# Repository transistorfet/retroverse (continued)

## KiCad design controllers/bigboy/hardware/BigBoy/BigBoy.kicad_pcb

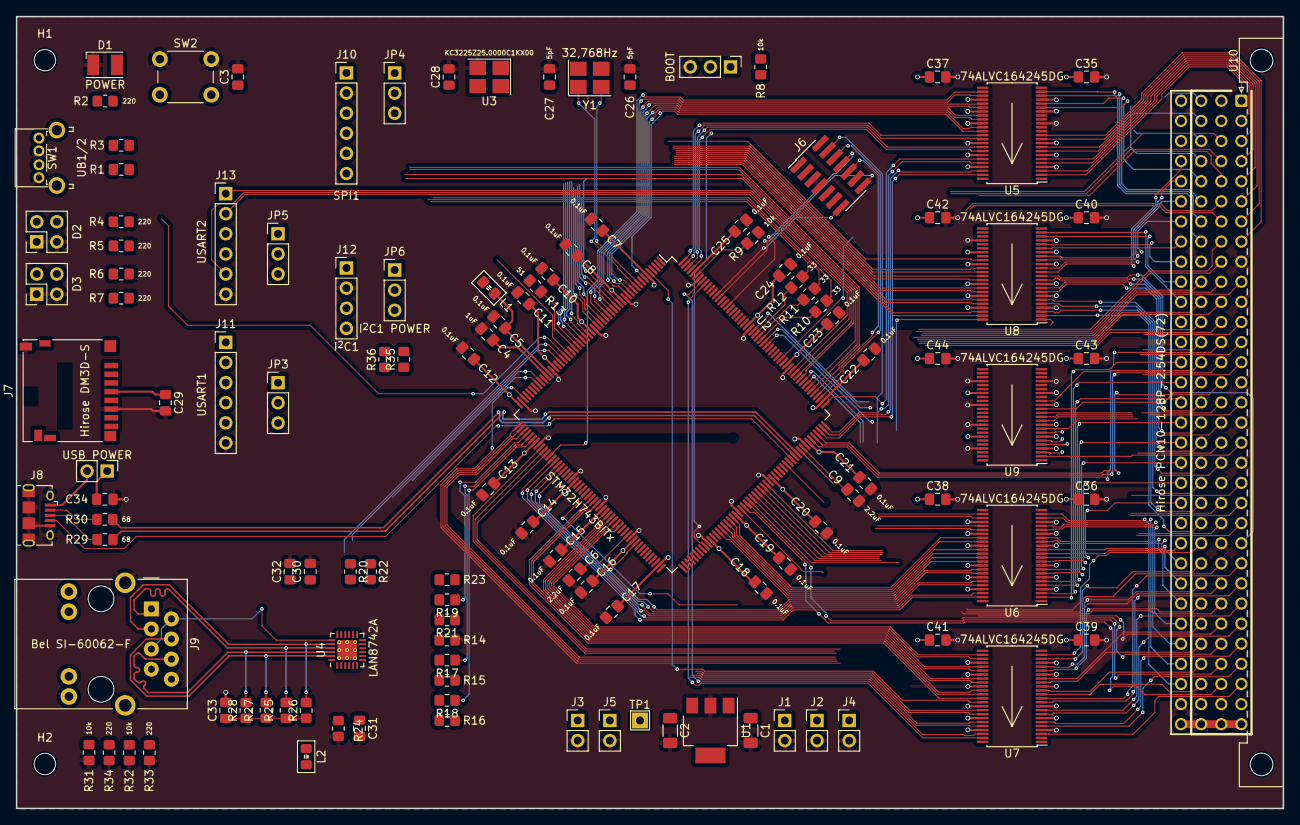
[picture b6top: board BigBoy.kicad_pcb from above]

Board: 4 copper layers, 160.0 x 100.0 mm, 120 parts (0 on the bottom side), 282 nets.

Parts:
C1, C2: 4.7uF; C_1206_3216Metric_Pad1.33x1.80mm_HandSolder
C3, C5, C7, C8, C10, C11, C12, C13, C14, C15, C16, C17, C18, C19, C20, C21, C22, C23, C24, C25, C28, C29, C30, C31, C32, C34, C35, C36, C37, C38, C39, C40, C41, C42, C43, C44: 0.1uF; C_0805_2012Metric_Pad1.18x1.45mm_HandSolder
C4: 1uF; C_0805_2012Metric_Pad1.18x1.45mm_HandSolder
C6, C9: 2.2uF; C_0805_2012Metric_Pad1.18x1.45mm_HandSolder
C26, C27: 5pF; C_0805_2012Metric_Pad1.18x1.45mm_HandSolder
C33: 10uF; C_0805_2012Metric_Pad1.18x1.45mm_HandSolder
D1: POWER; LED_PLCC-2_3.4x3.0mm_KA
D2: Dialight 5530188F; Dialight 553-0xxxF
D3: Dialight 5530177F; Dialight 553-0xxxF
H1, H2: MountingHole; MountingHole_2.7mm_M2.5_DIN965
J1, J2, J4: 5V; PinHeader_1x02_P2.54mm_Vertical
J3, J5: 3.3V; PinHeader_1x02_P2.54mm_Vertical
J6: Conn_ST_STDC14; PinHeader_2x07_P1.27mm_Vertical_SMD
J7: Hirose DM3D-S; microSD_HC_Hirose_DM3D-SF
J8: Amphenol 10118194-0001LF; USB_Micro-B_Amphenol_10118194_Horizontal
J9: Bel SI-60062-F; RJ45_Bel_SI-60062-F
J10: SPI1; PinHeader_1x06_P2.54mm_Vertical
J11: USART1; PinHeader_1x06_P2.54mm_Vertical
J12: I^{2}C1; PinHeader_1x04_P2.54mm_Vertical
J13: USART2; PinHeader_1x06_P2.54mm_Vertical
JP1: BOOT; PinHeader_1x03_P2.54mm_Vertical
JP2: USB POWER; PinHeader_1x02_P2.54mm_Vertical
JP3: USART1 POWER; PinHeader_1x03_P2.54mm_Vertical
JP4: SPI1 POWER; PinHeader_1x03_P2.54mm_Vertical
JP5: USART2 POWER; PinHeader_1x03_P2.54mm_Vertical
JP6: I^{2}C1 POWER; PinHeader_1x03_P2.54mm_Vertical
L1, L2: 600Ω @ 100MHz (MI0805K601R-10); Ferrite_0805_2012Metric_Pad1.15x1.40mm_BigPads
R1, R3, R8, R9, R14, R15, R16, R21, R22, R31, R32: 10k; R_0805_2012Metric_Pad1.20x1.40mm_HandSolder
R2, R4, R5, R6, R7, R33, R34: 220; R_0805_2012Metric_Pad1.20x1.40mm_HandSolder
R10, R11, R12, R17, R18, R19, R20: 33; R_0805_2012Metric_Pad1.20x1.40mm_HandSolder
R13: 51; R_0805_2012Metric_Pad1.20x1.40mm_HandSolder
R23: 1.5k; R_0805_2012Metric_Pad1.20x1.40mm_HandSolder
R24: 12.1k; R_0805_2012Metric_Pad1.20x1.40mm_HandSolder
R25, R26, R27, R28: 50; R_0805_2012Metric_Pad1.20x1.40mm_HandSolder
R29, R30: 68; R_0805_2012Metric_Pad1.20x1.40mm_HandSolder
R35, R36: 4.7k; R_0805_2012Metric_Pad1.20x1.40mm_HandSolder
SW1: UB1/2; E-Switch TL2243
SW2: ~{RESET}; SW_PUSH_6mm
TP1: 3.3V; TestPoint_THTPad_2.0x2.0mm_Drill1.0mm
U1: AP7361EA-33E-13; SOT-223
U2: STM32H743BITx; LQFP-208_28x28mm_P0.5mm
U3: KC3225Z25.0000C1KX00; Crystal_SMD_3225-4Pin_3.2x2.5mm_HandSoldering
U4: LAN8742A; VQFN-24-1EP_4x4mm_P0.5mm_EP2.5x2.5mm_ThermalVias
U5, U6, U7, U8, U9: 74ALVC164245DG; TSSOP-48_6.1x12.5mm_P0.5mm
U10: Hirose PCN10-128P-2.54DS(72); DIN41612_C_4x32_Male_Horizontal_THT
Y1: 32,768Hz; Crystal_SMD_3225-4Pin_3.2x2.5mm_HandSoldering

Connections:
+3.3V: C2.1, C7.1, C8.1, C10.1, C11.1, C12.1, C13.1, C14.1, C15.1, C16.1, C17.1, C18.1, C19.1, C20.1, C21.1, C22.1, C23.1, C24.1, C25.1, C28.1, C29.1, C30.1, C37.1, C38.1, C41.1, C42.1, C44.1, J3.1, J5.1, J6.3 (VCC), J7.4 (VDD), JP3.3 (B), JP4.3 (B), JP5.3 (B), JP6.3 (B), L1.2, L2.2, R1.1, R2.1, R3.1, R8.1, R9.1, R15.1, R16.1, R21.1, R22.1, R23.1, TP1.1, U1.3 (VO), U2.6 (VBAT), U2.15 (VDD), U2.26 (VDD), U2.39 (VDD), U2.52 (VDD), U2.59 (VDD), U2.73 (VDD), U2.83 (VDD), U2.94 (VDD), U2.103 (VDD), U2.115 (VDD), U2.124 (VDD), U2.137 (VDD33_USB), U2.150 (VDD), U2.158 (VDD), U2.171 (VDD), U2.185 (VDD), U2.204 (VDD), U3.1 (INH), U3.4 (VCC), U4.9 (VDDIO), U5.31 (VCCa), U5.42 (VCCa), U6.31 (VCCa), U6.42 (VCCa), U7.31 (VCCa), U7.42 (VCCa), U8.31 (VCCa), U8.42 (VCCa), U9.31 (VCCa), U9.42 (VCCa)
+5V: C1.1, C34.1, C35.2, C36.2, C39.2, C40.2, C43.2, J1.1, J2.1, J4.1, JP2.1 (A), JP3.1 (A), JP4.1 (A), JP5.1 (A), JP6.1 (A), U1.1 (VI), U5.7 (VCCb), U5.18 (VCCb), U6.7 (VCCb), U6.18 (VCCb), U7.7 (VCCb), U7.18 (VCCb), U8.7 (VCCb), U8.18 (VCCb), U9.7 (VCCb), U9.18 (VCCb), U10.a32 (+5V), U10.b32 (+5V), U10.c32 (+5V), U10.d1 (+5V), U10.d13 (+5V), U10.d32 (+5V)
/IO/RD+: J9.4 (RD+), R27.2, U4.23 (RXP)
/IO/RD-: J9.6 (RD-), R28.2, U4.22 (RXN)
/IO/TD+: J9.1 (TD+), R25.2, U4.21 (TXP)
/IO/TD-: J9.3 (TD-), R26.2, U4.20 (TXN)
AH_DIR: U2.54 (PA5), U6.24 (DIR2)
AL_DIR: U2.55 (PA6), U5.1 (DIR1), U5.24 (DIR2), U6.1 (DIR1)
CLK_25M: R13.2, U3.3 (CLK), U4.5 (XTAL1/CLKIN)
DH_DIR: U2.62 (PB1), U8.1 (DIR1), U8.24 (DIR2)
DL_DIR: U2.63 (PB2), U7.1 (DIR1), U7.24 (DIR2)
GND: C1.2, C2.2, C3.2, C4.1, C5.1, C6.2, C7.2, C8.2, C9.2, C10.2, C11.2, C12.2, C13.2, C14.2, C15.2, C16.2, C17.2, C18.2, C19.2, C20.2, C21.2, C22.2, C23.2, C24.2, C25.2, C26.2, C27.2, C28.2, C29.2, C30.2, C31.2, C32.2, C33.2, C34.2, C35.1, C36.1, C37.2, C38.2, C39.1, C40.1, C41.2, C42.2, C43.1, C44.2, D1.1 (K), D2.1 (A1), D2.3 (A2), D3.1 (A1), D3.3 (A2), J1.2, J2.2, J3.2, J4.2, J5.2, J6.5 (GND), J6.7 (GND), J6.11 (GNDDetect), J7.6 (VSS), J7.10 (SHIELD), J8.5 (GND), J8.6 (Shield), J9.8, J9.SH, J10.2, J11.6, J12.2, J13.6, JP1.3 (B), R14.2, R24.2, R31.2, R32.2, R33.2, R34.2, SW1.1 (C), SW1.3 (C), SW2.1, U1.2 (GND), U2.14 (VSS), U2.25 (VSS), U2.40 (VSSA), U2.51 (VSS), U2.60 (VSS), U2.72 (VSS), U2.82 (VSS), U2.93 (VSS), U2.114 (VSS), U2.125 (VSS), U2.136 (VSS), U2.149 (VSS), U2.170 (VSS), U2.184 (VSS), U2.202 (VSS), U3.2 (GND), U4.25 (VSS), U5.4 (GND), U5.10 (GND), U5.15 (GND), U5.21 (GND), U5.28 (GND), U5.34 (GND), U5.39 (GND), U5.45 (GND), U6.4 (GND), U6.10 (GND), U6.15 (GND), U6.21 (GND), U6.28 (GND), U6.34 (GND), U6.39 (GND), U6.45 (GND), U7.4 (GND), U7.10 (GND), U7.15 (GND), U7.21 (GND), U7.28 (GND), U7.34 (GND), U7.39 (GND), U7.45 (GND), U8.4 (GND), U8.10 (GND), U8.15 (GND), U8.21 (GND), U8.28 (GND), U8.34 (GND), U8.39 (GND), U8.45 (GND), U9.4 (GND), U9.10 (GND), U9.15 (GND), U9.21 (GND), U9.28 (GND), U9.34 (GND), U9.39 (GND), U9.45 (GND), U10.a9 (GND), U10.a11 (GND), U10.a15 (GND), U10.a17 (GND), U10.a19 (GND), U10.b20 (GND), U10.b23 (GND), U10.c9 (GND), U10.d2 (GND), U10.d12 (GND), U10.d22 (GND), U10.d31 (GND)
I2C_SCL: J12.3, R35.2, U2.198 (PB8)
I2C_SDA: J12.4, R36.2, U2.199 (PB9)
LA0: U2.200 (PE0), U7.47 (A0)
LA1: U2.201 (PE1), U7.46 (A1)
LA2: U2.1 (PE2), U7.44 (A2)
LA3: U2.2 (PE3), U7.43 (A3)
LA4: U2.3 (PE4), U7.41 (A4)
LA5: U2.4 (PE5), U7.40 (A5)
LA6: U2.5 (PE6), U7.38 (A6)
LA7: U2.79 (PE7), U7.37 (A7)
LA8: U2.80 (PE8), U7.36 (A8)
LA9: U2.81 (PE9), U7.35 (A9)
LA10: U2.84 (PE10), U7.33 (A10)
LA11: U2.85 (PE11), U7.32 (A11)
LA12: U2.86 (PE12), U7.30 (A12)
LA13: U2.87 (PE13), U7.29 (A13)
LA14: U2.88 (PE14), U7.27 (A14)
LA15: U2.89 (PE15), U7.26 (A15)
LA16: U2.16 (PF0), U8.47 (A0)
LA17: U2.17 (PF1), U8.46 (A1)
LA18: U2.18 (PF2), U8.44 (A2)
LA19: U2.22 (PF3), U8.43 (A3)
LA20: U2.23 (PF4), U8.41 (A4)
LA21: U2.24 (PF5), U8.40 (A5)
LA22: U2.27 (PF6), U8.38 (A6)
LA23: U2.28 (PF7), U8.37 (A7)
LA24: U2.29 (PF8), U8.36 (A8)
LA25: U2.30 (PF9), U8.35 (A9)
LA26: U2.31 (PF10), U8.33 (A10)
LA27: U2.70 (PF11), U8.32 (A11)
LA28: U2.71 (PF12), U8.30 (A12)
LA29: U2.74 (PF13), U8.29 (A13)
LA30: U2.75 (PF14), U8.27 (A14)
LA31: U2.76 (PF15), U8.26 (A15)
LAM0: U2.132 (PG5), U9.40 (A5)
LAM1: U2.133 (PG6), U9.38 (A6)
LAM2: U2.134 (PG7), U9.37 (A7)
LAM3: U2.135 (PG8), U9.36 (A8)
LAM4: U2.178 (PG9), U9.35 (A9)
LAM5: U2.179 (PG10), U9.33 (A10)
LD0: U2.154 (PI0), U5.47 (A0)
LD1: U2.155 (PI1), U5.46 (A1)
LD2: U2.156 (PI2), U5.44 (A2)
LD3: U2.157 (PI3), U5.43 (A3)
LD4: U2.205 (PI4), U5.41 (A4)
LD5: U2.206 (PI5), U5.40 (A5)
LD6: U2.207 (PI6), U5.38 (A6)
LD7: U2.208 (PI7), U5.37 (A7)
LD8: U2.7 (PI8), U5.36 (A8)
LD9: U2.11 (PI9), U5.35 (A9)
LD10: U2.12 (PI10), U5.33 (A10)
LD11: U2.13 (PI11), U5.32 (A11)
LD12: U2.19 (PI12), U5.30 (A12)
LD13: U2.20 (PI13), U5.29 (A13)
LD14: U2.21 (PI14), U5.27 (A14)
LD15: U2.64 (PI15), U5.26 (A15)
LD16: U2.65 (PJ0), U6.47 (A0)
LD17: U2.66 (PJ1), U6.46 (A1)
LD18: U2.67 (PJ2), U6.44 (A2)
LD19: U2.68 (PJ3), U6.43 (A3)
LD20: U2.69 (PJ4), U6.41 (A4)
LD21: U2.95 (PJ5), U6.40 (A5)
LD22: U2.118 (PJ6), U6.38 (A6)
LD23: U2.119 (PJ7), U6.37 (A7)
LD24: U2.120 (PJ8), U6.36 (A8)
LD25: U2.121 (PJ9), U6.35 (A9)
LD26: U2.122 (PJ10), U6.33 (A10)
LD27: U2.123 (PJ11), U6.32 (A11)
LD28: U2.174 (PJ12), U6.30 (A12)
LD29: U2.175 (PJ13), U6.29 (A13)
LD30: U2.176 (PJ14), U6.27 (A14)
LD31: U2.177 (PJ15), U6.26 (A15)
unnamed: C6.1, U2.92 (VCAP)
unnamed: C9.1, U2.148 (VCAP)
unnamed: D1.2 (A), R2.2
unnamed: D2.2 (K1), R4.2
unnamed: D2.4 (K2), R5.2
unnamed: D3.2 (K1), R6.2
unnamed: D3.4 (K2), R7.2
unnamed: J8.3 (D+), R29.1
unnamed: J8.2 (D-), R30.1
unnamed: J8.1 (VBUS), JP2.2 (B)
unnamed: J9.L2, R34.1
unnamed: J9.L4, R33.1
unnamed: C32.1, C33.1, J9.2 (TCT), J9.5 (RCT), L2.1, R25.1, R26.1, R27.1, R28.1, U4.1 (VDD2A), U4.19 (VDD1A)
unnamed: J10.1, JP4.2 (C)
unnamed: J11.4, JP3.2 (C)
unnamed: J12.1, JP6.2 (C), R35.1, R36.1
unnamed: J13.4, JP5.2 (C)
unnamed: JP1.1 (A), R8.2
unnamed: JP1.2 (C), U2.197 (BOOT0)
unnamed: C26.1, U2.9 (PC14), Y1.2
unnamed: C27.1, U2.10 (PC15), Y1.1
unnamed: R10.1, U2.180 (PG11)
unnamed: R11.1, U2.181 (PG12)
unnamed: R12.1, U2.182 (PG13)
unnamed: R13.1, U2.32 (PH0)
unnamed: R9.2, U2.203 (PDR_ON)
unnamed: C4.2, C5.2, L1.1, U2.41 (VREF+), U2.42 (VDDA)
unnamed: R19.2, R21.2, U4.11 (CRS_DV/MODE2)
unnamed: J9.L1, R31.1, U4.3 (LED1/REGOFF)
unnamed: R24.1, U4.24 (RBIAS)
unnamed: R15.2, R17.2, U4.8 (RXD0/MODE0)
unnamed: R16.2, R18.2, U4.7 (RXD1/MODE1)
unnamed: R14.1, U4.10 (RXER/PHYAD0)
unnamed: C31.1, U4.6 (VDDCR)
unnamed: R20.2, R22.2, U4.14 (~INT/REFCLKO)
RMII_CRS_DV: R19.1, U2.56 (PA7)
RMII_MDC: U2.36 (PC1), U4.13 (MDC)
RMII_MDIO: R23.2, U2.45 (PA2), U4.12 (MDIO)
RMII_REF_CLK: R20.1, U2.44 (PA1)
RMII_RXD0: R17.1, U2.57 (PC4)
RMII_RXD1: R18.1, U2.58 (PC5)
RMII_TXD0: R12.2, U4.17 (TXD0)
RMII_TXD1: R11.2, U4.18 (TXD1)
RMII_TXEN: R10.2, U4.16 (TXEN)
RMII_nINT: J9.L3, R32.1, U2.37 (PC2_C), U4.2 (LED2/~INTSEL)
SDIO_CLK: J7.5 (CLK), U2.163 (PC12)
SDIO_CMD: J7.3 (CMD), U2.166 (PD2)
SDIO_D0: J7.7 (DAT0), U2.140 (PC8)
SDIO_D1: J7.8 (DAT1), U2.141 (PC9)
SDIO_D2: J7.1 (DAT2), U2.161 (PC10)
SDIO_D3: J7.2 (DAT3/CD), U2.162 (PC11)
SDIO_DET: J7.9 (DET), U2.38 (PC3_C)
SPI_SCK: J10.5, U2.105 (PB13)
SPI_SDI: J10.4, U2.107 (PB15)
SPI_SDO: J10.3, U2.106 (PB14)
TCK/SWCLK: J6.6 (JCLK/SWCLK), U2.159 (PA14)
TDI: J6.10 (JTDI/NC), U2.160 (PA15)
TDO/SWO: J6.8 (JTDO/SWO), U2.192 (PB3)
TMS/SWDIO: J6.4 (JTMS/SWDIO), U2.147 (PA13)
UB1: R1.2, SW1.2 (D), U2.143 (PA9)
UB2: R3.2, SW1.4 (D), U2.110 (PD10)
UL1: R4.1, U2.35 (PC0)
UL2: R5.1, U2.138 (PC6)
UL3: R6.1, U2.139 (PC7)
UL4: R7.1, U2.8 (PC13)
USART1_CTS: J11.1, U2.111 (PD11)
USART1_RTS: J11.5, U2.112 (PD12)
USART1_RX: J11.3, U2.109 (PD9)
USART1_TX: J11.2, U2.108 (PD8)
USART2_CTS: J13.1, U2.167 (PD3)
USART2_RTS: J13.5, U2.168 (PD4)
USART2_RX: J13.3, U2.172 (PD6)
USART2_TX: J13.2, U2.169 (PD5)
USB_DN: R30.2, U2.145 (PA11)
USB_DP: R29.2, U2.146 (PA12)
USB_ID: J8.4 (ID), U2.144 (PA10)
VA1: U7.3 (B1), U10.a30 (A01)
VA2: U7.5 (B2), U10.a29 (A02)
VA3: U7.6 (B3), U10.a28 (A03)
VA4: U7.8 (B4), U10.a27 (A04)
VA5: U7.9 (B5), U10.a26 (A05)
VA6: U7.11 (B6), U10.a25 (A06)
VA7: U7.12 (B7), U10.a24 (A07)
VA8: U7.13 (B8), U10.c30 (A8)
VA9: U7.14 (B9), U10.c29 (A9)
VA10: U7.16 (B10), U10.c28 (A10)
VA11: U7.17 (B11), U10.c27 (A11)
VA12: U7.19 (B12), U10.c26 (A12)
VA13: U7.20 (B13), U10.c25 (A13)
VA14: U7.22 (B14), U10.c24 (A14)
VA15: U7.23 (B15), U10.c23 (A15)
VA16: U8.2 (B0), U10.c22 (A16)
VA17: U8.3 (B1), U10.c21 (A17)
VA18: U8.5 (B2), U10.c20 (A18)
VA19: U8.6 (B3), U10.c19 (A19)
VA20: U8.8 (B4), U10.c18 (A20)
VA21: U8.9 (B5), U10.c17 (A21)
VA22: U8.11 (B6), U10.c16 (A22)
VA23: U8.12 (B7), U10.c15 (A23)
VA24: U8.13 (B8), U10.d4 (A24)
VA25: U8.14 (B9), U10.d5 (A25)
VA26: U8.16 (B10), U10.d6 (A26)
VA27: U8.17 (B11), U10.d7 (A27)
VA28: U8.19 (B12), U10.d8 (A28)
VA29: U8.20 (B13), U10.d9 (A29)
VA30: U8.22 (B14), U10.d10 (A30)
VA31: U8.23 (B15), U10.d11 (A31)
VAM0: U9.9 (B5), U10.b16 (AM0)
VAM1: U9.11 (B6), U10.b17 (AM1)
VAM2: U9.12 (B7), U10.b18 (AM2)
VAM3: U9.13 (B8), U10.b19 (AM3)
VAM4: U9.14 (B9), U10.a23 (AM4)
VAM5: U9.16 (B10), U10.c14 (AM5)
VCP_RX: J6.13 (VCP_RX), U2.196 (PB7)
VCP_TX: J6.14 (VCP_TX), U2.195 (PB6)
VD0: U5.2 (B0), U10.a1 (D00)
VD1: U5.3 (B1), U10.a2 (D01)
VD2: U5.5 (B2), U10.a3 (D02)
VD3: U5.6 (B3), U10.a4 (D03)
VD4: U5.8 (B4), U10.a5 (D04)
VD5: U5.9 (B5), U10.a6 (D05)
VD6: U5.11 (B6), U10.a7 (D06)
VD7: U5.12 (B7), U10.a8 (D07)
VD8: U5.13 (B8), U10.c1 (D08)
VD9: U5.14 (B9), U10.c2 (D09)
VD10: U5.16 (B10), U10.c3 (D10)
VD11: U5.17 (B11), U10.c4 (D11)
VD12: U5.19 (B12), U10.c5 (D12)
VD13: U5.20 (B13), U10.c6 (D13)
VD14: U5.22 (B14), U10.c7 (D14)
VD15: U5.23 (B15), U10.c8 (D15)
VD16: U6.2 (B0), U10.d14 (D16)
VD17: U6.3 (B1), U10.d15 (D17)
VD18: U6.5 (B2), U10.d16 (D18)
VD19: U6.6 (B3), U10.d17 (D19)
VD20: U6.8 (B4), U10.d18 (D20)
VD21: U6.9 (B5), U10.d19 (D21)
VD22: U6.11 (B6), U10.d20 (D22)
VD23: U6.12 (B7), U10.d21 (D23)
VD24: U6.13 (B8), U10.d23 (D24)
VD25: U6.14 (B9), U10.d24 (D25)
VD26: U6.16 (B10), U10.d25 (D26)
VD27: U6.17 (B11), U10.d26 (D27)
VD28: U6.19 (B12), U10.d27 (D28)
VD29: U6.20 (B13), U10.d28 (D29)
VD30: U6.22 (B14), U10.d29 (D30)
VD31: U6.23 (B15), U10.d30 (D31)
~AH_OE: U2.50 (PA3), U6.25 (~OE2)
~AL_OE: U2.53 (PA4), U5.25 (~OE2), U5.48 (~OE1), U6.48 (~OE1)
~CTRL_DIR: U2.194 (PB5), U9.1 (DIR1), U9.24 (DIR2)
~CTRL_OE: U2.193 (PB4), U9.25 (~OE2), U9.48 (~OE1)
~DH_OE: U2.142 (PA8), U8.25 (~OE2), U8.48 (~OE1)
~DL_OE: U2.61 (PB0), U7.25 (~OE2), U7.48 (~OE1)
~LAS: U2.77 (PG0), U9.47 (A0)
~LDS0: U2.129 (PG2), U9.44 (A2)
~LDS1: U2.78 (PG1), U9.46 (A1)
~LLWORD: U2.131 (PG4), U9.41 (A4)
~LWRITE: U2.130 (PG3), U9.43 (A3)
~RESET: C3.1, J6.12 (~RST), SW2.2, U2.34 (NRST), U4.15 (~RST)
~SPI_CS: J10.6, U2.104 (PB12)
~VACFAIL: U2.113 (PD13), U10.b3 (~ACFAIL)
~VAS: U9.2 (B0), U10.a18 (~AS)
~VBBSY: U2.46 (PH2), U10.b1 (~BBSY)
~VBCLR: U2.47 (PH3), U10.b2 (~BCLR)
~VBERR: U2.191 (PG15), U10.c11 (~BERR)
~VBG0IN: U2.48 (PH4), U10.b4 (~BG0IN)
~VBG0OUT: U2.49 (PH5), U10.b5 (~BG0OUT)
~VBG1IN: U2.96 (PH6), U10.b6 (~BG1IN)
~VBG1OUT: U2.97 (PH7), U10.b7 (~BG1OUT)
~VBG2IN: U2.98 (PH8), U10.b8 (~BG2IN)
~VBG2OUT: U2.99 (PH9), U10.b9 (~BG2OUT)
~VBG3IN: U2.100 (PH10), U10.b10 (~BG3IN)
~VBG3OUT: U2.101 (PH11), U10.b11 (~BG3OUT)
~VBR0: U2.102 (PH12), U10.b12 (~BR0)
~VBR1: U2.151 (PH13), U10.b13 (~BR1)
~VBR2: U2.152 (PH14), U10.b14 (~BR2)
~VBR3: U2.153 (PH15), U10.b15 (~BR3)
~VDS0: U9.5 (B2), U10.a13 (~DS0)
~VDS1: U9.3 (B1), U10.a12 (~DS1)
~VDTACK: U2.183 (PG14), U10.a16 (~DTACK)
~VIACKIN: U2.164 (PD0), U10.a21 (~IACKIN)
~VIACKOUT: U2.165 (PD1), U10.a22 (~IACKOUT)
~VIACK: U2.126 (PK0), U10.a20 (~IACK)
~VIRQ1: U2.127 (PK1), U10.b30 (~IRQ1)
~VIRQ2: U2.128 (PK2), U10.b29 (~IRQ2)
~VIRQ3: U2.186 (PK3), U10.b28 (~IRQ3)
~VIRQ4: U2.187 (PK4), U10.b27 (~IRQ4)
~VIRQ5: U2.188 (PK5), U10.b26 (~IRQ5)
~VIRQ6: U2.189 (PK6), U10.b25 (~IRQ6)
~VIRQ7: U2.190 (PK7), U10.b24 (~IRQ7)
~VLWORD: U9.8 (B4), U10.c13 (~LWORD)
~VRETRY: U2.173 (PD7), U10.d3 (~RETRY)
~VSERCLK: U2.90 (PB10), U10.b21 (SERCLK)
~VSERDAT: U2.91 (PB11), U10.b22 (SERDAT)
~VSYSCLK: U2.117 (PD15), U10.a10 (SYSCLK)
~VSYSFAIL: U2.116 (PD14), U10.c10 (~SYSFAIL)
~VSYSRESET: U2.43 (PA0), U10.c12 (~SYSRESET)
~VWRITE: U9.6 (B3), U10.a14 (~WRITE)

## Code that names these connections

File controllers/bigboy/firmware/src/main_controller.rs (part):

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    let gpioh = dp.GPIOH.split(ccdr.peripheral.GPIOH);
    let gpiok = dp.GPIOK.split(ccdr.peripheral.GPIOK);

    let mut led1 = gpioc.pc0.into_push_pull_output();
    let mut led2 = gpioa.pa3.into_push_pull_output();
    let mut led3 = gpioa.pa4.into_push_pull_output();
    let mut led4 = gpioc.pc13.into_push_pull_output();
    let button1 = gpioa.pa9.into_floating_input();


    let mut dl_oe = gpioa.pa5.into_push_pull_output();
    let mut dl_dir = gpioa.pa6.into_push_pull_output();
    let mut dh_oe = gpioc.pc6.into_push_pull_output();
    let mut dh_dir = gpioc.pc7.into_push_pull_output();
    let mut al_oe = gpiob.pb0.into_push_pull_output();
    let mut al_dir = gpiob.pb2.into_push_pull_output();
    let mut ah_oe = gpioa.pa8.into_push_pull_output();
    let mut ah_dir = gpiob.pb1.into_push_pull_output();
    let mut ctrl_oe = gpiob.pb4.into_push_pull_output();
    let mut ctrl_dir = gpiob.pb5.into_push_pull_output();
    al_oe.set_high();
    al_dir.set_high(); // low = INPUT (from bus), high = OUTPUT (to bus)
    ah_oe.set_high();
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    ctrl_dir.set_high(); // low = INPUT (from bus), high = OUTPUT (to bus)


    let al = TransceiverPins::new(al_oe, al_dir);
    let ah = TransceiverPins::new(ah_oe, ah_dir);
    let dl = TransceiverPins::new(dl_oe, dl_dir);
    let dh = TransceiverPins::new(dh_oe, dh_dir);
    let ctrl = TransceiverPins::new(ctrl_oe, ctrl_dir);

    ccdr.peripheral.GPIOE.enable().reset();
    ccdr.peripheral.GPIOF.enable().reset();
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    let address_bus = BusPins::new("address", ah, al, dp.GPIOF, dp.GPIOE);
    let data_bus = BusPins::new("data", dh, dl, dp.GPIOJ, dp.GPIOI);

    let address_strobe = gpiog.pg0.into_push_pull_output();
    let data_strobe0 = gpiog.pg2.into_push_pull_output();
    let data_strobe1 = gpiog.pg1.into_push_pull_output();
    let write = gpiog.pg3.into_push_pull_output();
    let lword = gpiog.pg4.into_push_pull_output();

    let am0 = gpiog.pg5.into_push_pull_output();
    let am1 = gpiog.pg6.into_push_pull_output();
    let am2 = gpiog.pg7.into_push_pull_output();
    let am3 = gpiog.pg8.into_push_pull_output();
    let am4 = gpiog.pg9.into_push_pull_output();
    let am5 = gpiog.pg10.into_push_pull_output();
    let address_modifier = AddressModifierPins::new(am0, am1, am2, am3, am4, am5);

    let dtack = gpiog.pg14.into_floating_input();
    let berr = gpiog.pg15.into_floating_input();
    let retry = gpiod.pd7.into_floating_input();

    let control_bus = ControlPins::new(
        ctrl,
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
    let mut vmebus = DataTransferBus::new(control_bus, address_bus, data_bus);

    let sysreset = gpioa.pa0.into_open_drain_output_in_state(PinState::High);
    let acfail = gpiod.pd13.into_open_drain_output_in_state(PinState::High);
    let sysfail = gpiod.pd14.into_open_drain_output_in_state(PinState::High);

    let bbsy = gpioh.ph2.into_open_drain_output_in_state(PinState::High).erase();
    let bclr = gpioh.ph3.into_open_drain_output_in_state(PinState::High).erase();

    let br0 = gpioh.ph12.into_open_drain_output_in_state(PinState::High).erase();
    let br1 = gpioh.ph13.into_open_drain_output_in_state(PinState::High).erase();
    let br2 = gpioh.ph14.into_open_drain_output_in_state(PinState::High).erase();
    let br3 = gpioh.ph15.into_open_drain_output_in_state(PinState::High).erase();

    let bg0in = gpioh.ph4.into_floating_input().erase();
    let bg0out = gpioh.ph5.into_push_pull_output_in_state(PinState::High).erase();
    let bg1in = gpioh.ph6.into_floating_input().erase();
    let bg1out = gpioh.ph7.into_push_pull_output_in_state(PinState::High).erase();
    let bg2in = gpioh.ph8.into_floating_input().erase();
    let bg2out = gpioh.ph9.into_push_pull_output_in_state(PinState::High).erase();
    let bg3in = gpioh.ph10.into_floating_input().erase();
    let bg3out = gpioh.ph11.into_push_pull_output_in_state(PinState::High).erase();

    let arbitration = BusArbitration {
        bbsy,
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        bgout: [bg0out, bg1out, bg2out, bg3out],
    };

    let sysclk_pin = gpiod.pd15.into_alternate_af2();

    let (control, mut sysclk) = dp.TIM4
        .pwm_advanced(
            sysclk_pin,
            ccdr.peripheral.TIM4,
            &ccdr.clocks
        )
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    sysclk.enable();

    let mut delay = cp.SYST.delay(ccdr.clocks);
    //let mut output = gpioa.pa3.into_alternate();
    let mut timer = dp.TIM2.tick_timer(1.MHz(), ccdr.peripheral.TIM2, &ccdr.clocks);

    let tx = gpiod.pd8.into_alternate();
    let rx = gpiod.pd9.into_alternate();

    // Configure the serial peripheral
    let serial = dp
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    led4.set_high();

    // Configure the interrupt signals
    let iack = gpiok.pk0.into_open_drain_output_in_state(PinState::High);
    let irq = [
        gpiok.pk1.into_push_pull_output_in_state(PinState::High).erase(),
        gpiok.pk2.into_push_pull_output_in_state(PinState::High).erase(),
        gpiok.pk3.into_push_pull_output_in_state(PinState::High).erase(),
        gpiok.pk4.into_push_pull_output_in_state(PinState::High).erase(),
        gpiok.pk5.into_push_pull_output_in_state(PinState::High).erase(),
        gpiok.pk6.into_push_pull_output_in_state(PinState::High).erase(),
        gpiok.pk7.into_push_pull_output_in_state(PinState::High).erase(),
    ];

    let mut value = 0_u32;
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//! Demo for STM32H747I-DISCO eval board using the Real Time for the Masses
//! (RTIC) framework.
//!
//! STM32H747I-DISCO: RMII TXD1 is on PG12
//!
//! If you are using the following boards, you will need to change the TXD1 pin
//! assignment below!
//! NUCLEO-H743ZI2: RMII TXD1 is on PB13
//! NUCLEO-H745I-Q: RMII TXD1 is on PB13
//!
//! This demo responds to pings on 192.168.1.99 (IP address hardcoded below)
//!
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    struct LocalResources {
        net: Net<'static>,
        lan8742a: ethernet::phy::LAN8742A<ethernet::EthernetMAC>,
        link_led: gpio::gpioi::PI14<gpio::Output<gpio::PushPull>>,
    }

    #[init]
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        let gpioc = ctx.device.GPIOC.split(ccdr.peripheral.GPIOC);
        let gpiod = ctx.device.GPIOD.split(ccdr.peripheral.GPIOD);

        let mut led1 = gpioc.pc0.into_push_pull_output();
        let mut led2 = gpioa.pa3.into_push_pull_output();
        let mut led3 = gpioa.pa4.into_push_pull_output();
        let mut led4 = gpioc.pc13.into_push_pull_output();


        let mut al_oe = gpioa.pa5.into_push_pull_output();
        let mut al_dir = gpioa.pa6.into_push_pull_output();
        let mut ah_oe = gpioc.pc6.into_push_pull_output();
        let mut ah_dir = gpioc.pc7.into_push_pull_output();
        let mut dl_oe = gpiob.pb0.into_push_pull_output();
        let mut dl_dir = gpiob.pb2.into_push_pull_output();
        let mut dh_oe = gpioa.pa8.into_push_pull_output();
        let mut dh_dir = gpiob.pb1.into_push_pull_output();
        let mut ctrl_oe = gpiob.pb4.into_push_pull_output();
        let mut ctrl_dir = gpiob.pb5.into_push_pull_output();
        al_oe.set_high();
        al_dir.set_high(); // low = INPUT (from bus), high = OUTPUT (to bus)
        ah_oe.set_high();
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        //let gpioc = ctx.device.GPIOC.split(ccdr.peripheral.GPIOC);
        let gpiog = ctx.device.GPIOG.split(ccdr.peripheral.GPIOG);
        let gpioi = ctx.device.GPIOI.split(ccdr.peripheral.GPIOI);
        let mut link_led = gpioi.pi14.into_push_pull_output(); // LED3
        link_led.set_high();

        let rmii_ref_clk = gpioa.pa1.into_alternate();
        let rmii_mdio = gpioa.pa2.into_alternate();
        let rmii_mdc = gpioc.pc1.into_alternate();
        let rmii_crs_dv = gpioa.pa7.into_alternate();
        let rmii_rxd0 = gpioc.pc4.into_alternate();
        let rmii_rxd1 = gpioc.pc5.into_alternate();
        let rmii_tx_en = gpiog.pg11.into_alternate();
        let rmii_txd0 = gpiog.pg13.into_alternate();
        let rmii_txd1 = gpiog.pg12.into_alternate(); // STM32H747I-DISCO

        // Initialise ethernet...
        assert_eq!(ccdr.clocks.hclk().raw(), 200_000_000); // HCLK 200MHz
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    let gpioc = dp.GPIOC.split(ccdr.peripheral.GPIOC);
    let gpiog = dp.GPIOG.split(ccdr.peripheral.GPIOG);

    let mut led = gpioi.pi12.into_push_pull_output();

    let mut link_led = gpioi.pi14.into_push_pull_output(); // LED3
    link_led.set_high();

    let rmii_ref_clk = gpioa.pa1.into_alternate();
    let rmii_mdio = gpioa.pa2.into_alternate();
    let rmii_mdc = gpioc.pc1.into_alternate();
    let rmii_crs_dv = gpioa.pa7.into_alternate();
    let rmii_rxd0 = gpioc.pc4.into_alternate();
    let rmii_rxd1 = gpioc.pc5.into_alternate();
    let rmii_tx_en = gpiog.pg11.into_alternate();
    let rmii_txd0 = gpiog.pg13.into_alternate();
    let rmii_txd1 = gpiog.pg12.into_alternate();


    // Initialise ethernet...
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    let gpioc = dp.GPIOC.split(ccdr.peripheral.GPIOC);
    let gpiog = dp.GPIOG.split(ccdr.peripheral.GPIOG);

    let mut led = gpioi.pi12.into_push_pull_output();

    let mut delay = cp.SYST.delay(ccdr.clocks);

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/*
    let gpioj = dp.GPIOJ.split(ccdr.peripheral.GPIOJ);

    let mut output = gpioj.pj5.into_push_pull_output();
    let mut input = gpioj.pj6.into_push_pull_output();

    let mut delay = cp.SYST.delay(ccdr.clocks);
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
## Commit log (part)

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2023-09-04 Start of backplane and cpu card design
2023-09-30 Updated k30 CPU card
2023-10-01 Renamed BP8 to BUS8
2023-12-10 Committed changes to k30 board from Oct 9th 2023
2023-12-19 Added STM32H7-based controller schematic, and start of board layout
2023-12-21 STM32H7 PCB work in progress
2023-12-23 Reorganized to make it easier to group hardware and firmware files together
2023-12-28 Most of the routing for BigBoy is done
2023-12-28 Completed all connections for BigBoy
    Now it's just final checks and adjustments lefts
2023-12-30 BigBoy Rev.1 is complete and ready to order
2024-01-07 Added initial firmware
2024-08-05 Reorganized, and completed SystemBoard PCB
2024-08-05 Cleaned up readme
2024-08-31 Added SystemBoardSMT, renamed k30 boards, and added progress
2024-09-07 Updating with more work in progress
2024-09-07 Updated readmes
2024-09-25 Reorganized a bit
2024-09-27 Added SystemBoardSMT schematics
2024-10-13 Basic systemboard logic for bus arbitration is working and tested
2024-10-19 Schematics for k30p-VME more or less done
2024-10-23 WIP on k30p-VME
2024-10-27 Removed unstarted computie designs
2024-10-27 k30p-VME PCB work in progress
2024-11-12 Mostly finished k30p-VME board and frontpanel
2024-11-24 Added MemBird - Woodcock (16-bit VME memory card)
2024-11-27 MemBird - Woodcock Rev.1 Schematic is complete
2024-12-01 Finished the MemBird - Woodcock 16-bit memory board layout
2024-12-03 k30p-VME rev.1, MemBird Woodcock rev.1, and frontpanels
2024-12-21 Various findings from the first build of k30p-VME
2024-12-24 Working state during bringup just before the FTDI was broken
2024-12-30 Minor logic fixes for k30p and systemboard
2024-12-31 More fixes to the k30p logic and added dummy peripheral to systemboard
2025-01-04 Added images
2025-01-04 Updated with working logic
2025-01-13 Minor fixes and notes
2025-01-16 Fixed k30p running code from membird
    The issue turned out to be the DS0 and DS1 signals were swapped, but
    everything else was correct on both the memory card and the k30p, with
    the transceivers and which pins they were connected to. The k30p can
    now run the monitor from the memory card
2025-01-22 Updated errata for k30p
2025-01-27 Fixed the logic for the k30p, so it boots fully off the disk now
2025-01-27 Reorganized all subprojects into `components`
2025-01-28 Added big boy and frontpanel pictures
2025-01-28 Fixed board readmes
2025-01-28 Added readme for systemboard
2025-01-28 Fixed some links
2025-01-28 Fixed links
2025-01-30 Added note about other VME projects
2025-02-09 Added system reset logic to SystemBoard CPLD
    An extra capacitor needs to be installed to get power-on reset
    functionality, but pressing the reset button will now reset the whole
    system via the /SYSRESET signal on the VME bus, with a timer before the
    reset is released
2025-02-11 I thought I'd fixed the issue where two CPU cycles would sometimes occur per VME cycle
    Things were seemingly working after I increased the clock to 25MHz from
    12.5MHz, but it would read ATA sectors from the CF card that were all
    the same non-zero value, which wasn't the correct data at that sector.
    The problem in the logic analyzer traces was that CPU_AS would go high,
    and then low again, before VME_AS would go high. This was a problem
    especially for writing the sector number to the ATA registers, when the
2025-02-15 k30p logic: works as best as it has, but still can't ls /bin
    This uses an inverted clock, which should smooth out the clock a bit
    more, compensating for only using 2 gates for the clock circuit. It
    also rearranges the dsack logic a bit. I'm going to try clocking the
    dsack logic, and other more drastic changes to get the last issues out.
2025-02-17 Fixed systemboard bus logic to not hang
    I also went through a length weeks long debugging arc that thought it
    was the buslogic only to find it was the systemboard *and* the bus
    logic, and trying to focus on the buslogic to get the last bug sorted
    only to find it was actually a bug that happens on the k30-SBC as well,
    so it's not related to the logic most likely. Now I've fixed the system
    board bug and I need to debug the listing bug from the software side
2025-03-05 Added images of the schroff case
2025-03-05 Fixed link
2025-03-06 Changed license
2025-03-11 Added old files for SystemBoardPLCC
2025-03-11 Updated log
2026-03-02 Minor tweaks to rtl of k30p
    I've been trying to figure out this tty double char bug, and committing
    changes that were made over the last few months to a year
